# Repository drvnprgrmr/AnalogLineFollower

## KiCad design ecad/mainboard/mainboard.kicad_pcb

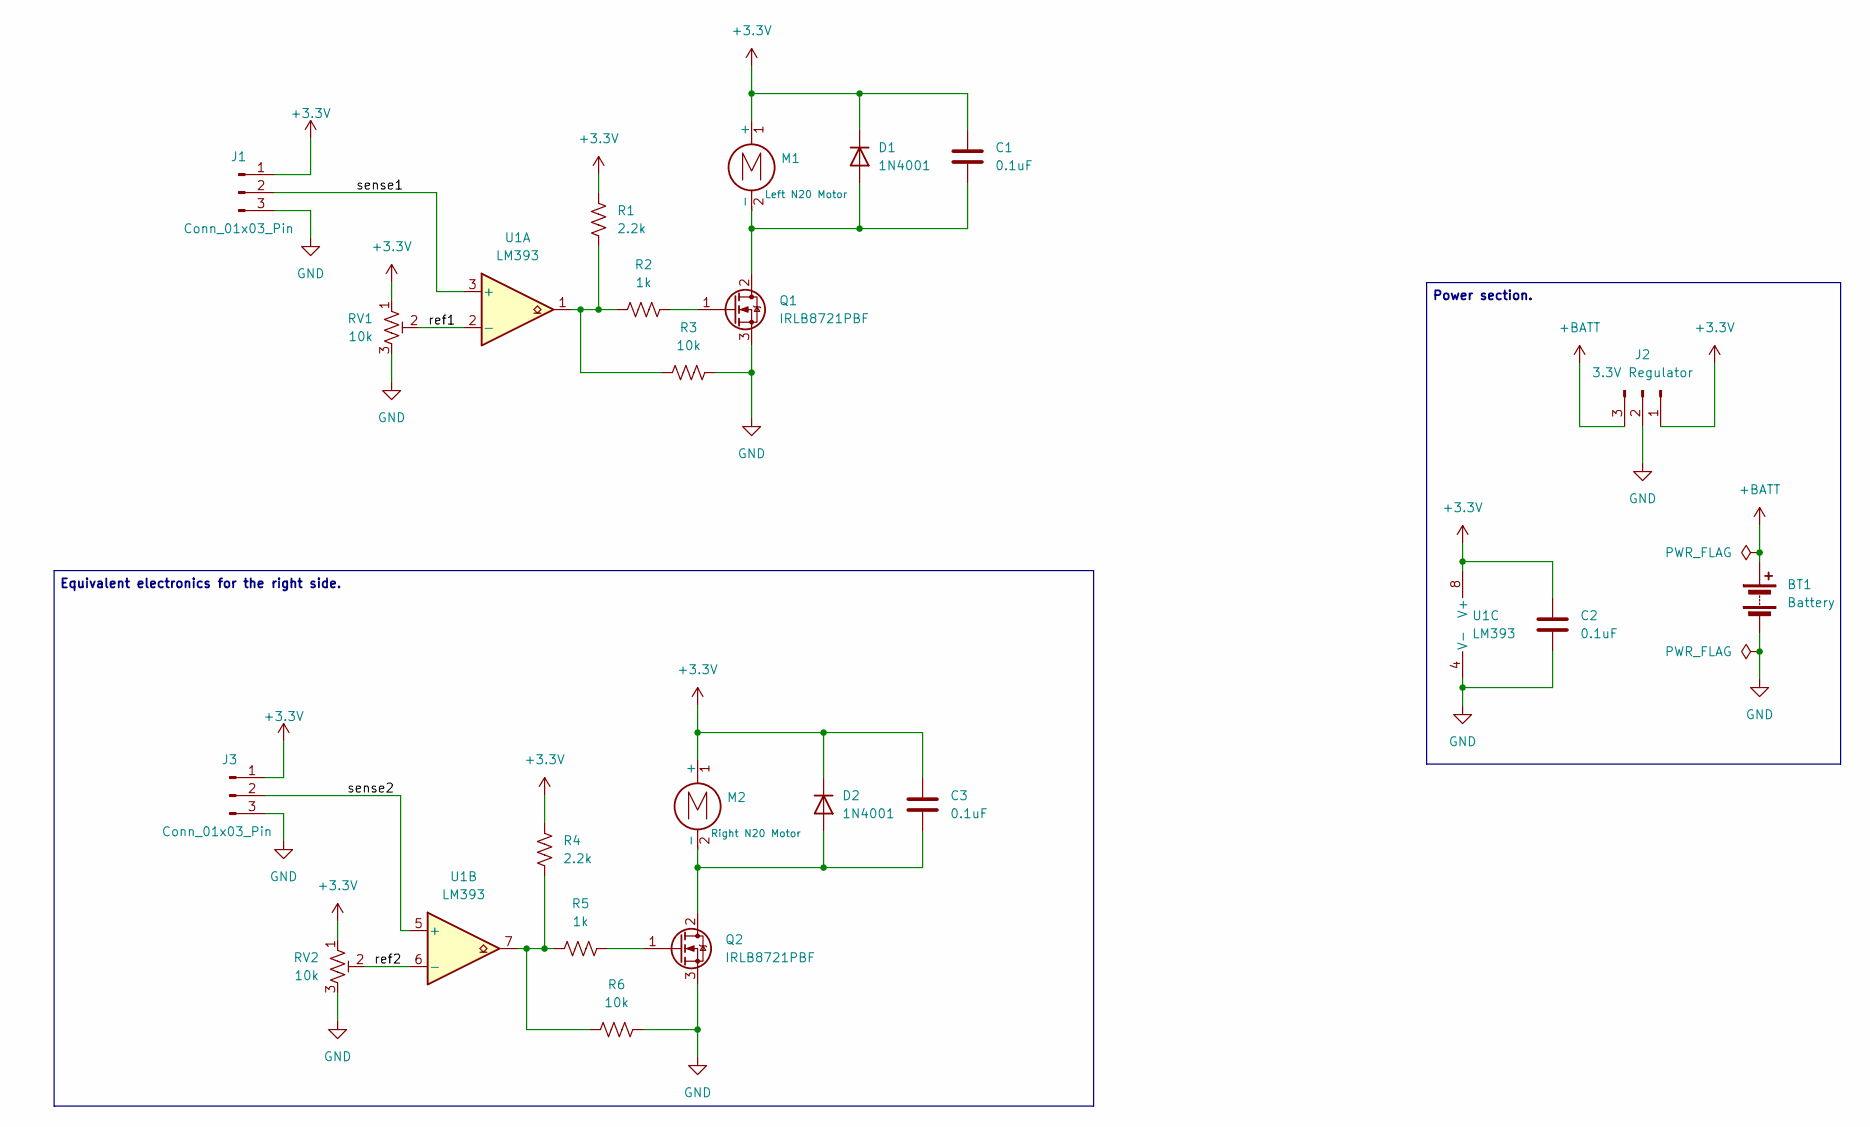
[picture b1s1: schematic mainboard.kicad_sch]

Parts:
BT1: Battery; TerminalBlock_4Ucon_1x02_P3.50mm_Vertical
C1, C2, C3: 0.1uF; C_Radial_D4.0mm_H7.0mm_P1.50mm
D1, D2: 1N4001; D_DO-41_SOD81_P10.16mm_Horizontal
J1, J3: Conn_01x03_Pin; PinHeader_1x03_P2.54mm_Horizontal
J2: 3.3V Regulator; PinHeader_1x03_P2.54mm_Vertical
M1: Left N20 Motor; JST_ZH_B2B-ZR_1x02_P1.50mm_Vertical
M2: Right N20 Motor; JST_ZH_B2B-ZR_1x02_P1.50mm_Vertical
Q1, Q2: IRLB8721PBF; TO-220-3_Vertical
R1, R4: 2.2k; R_Axial_DIN0207_L6.3mm_D2.5mm_P7.62mm_Horizontal
R2, R5: 1k; R_Axial_DIN0207_L6.3mm_D2.5mm_P7.62mm_Horizontal
R3, R6: 10k; R_Axial_DIN0207_L6.3mm_D2.5mm_P7.62mm_Horizontal
RV1, RV2: 10k; Potentiometer_Bourns_3296W_Vertical
U1: LM393; DIP-8_W7.62mm_Socket

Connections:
+3.3V: C1.1, C2.1, C3.1, D1.1 (K), D2.1 (K), J1.1, J2.1, J3.1, M1.1 (+), M2.1 (+), R1.2, R4.2, RV1.1, RV2.1, U1.8 (V+)
+BATT: BT1.1 (+), J2.3
/ref1: RV1.2, U1.2 (-)
/ref2: RV2.2, U1.6 (-)
/sense1: J1.2, U1.3 (+)
/sense2: J3.2, U1.5 (+)
GND: BT1.2 (-), C2.2, J1.3, J2.2, J3.3, Q1.3 (S), Q2.3 (S), R3.2, R6.2, RV1.3, RV2.3, U1.4 (V-)
unnamed: C1.2, D1.2 (A), M1.2 (-), Q1.2 (D)
unnamed: C3.2, D2.2 (A), M2.2 (-), Q2.2 (D)
unnamed: Q1.1 (G), R2.2
unnamed: Q2.1 (G), R5.2
unnamed: R1.1, R2.1, R3.1, U1.1
unnamed: R4.1, R5.1, R6.1, U1.7

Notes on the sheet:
Power section.
Equivalent electronics for the right side.

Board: 12 copper layers, 22 parts (0 on the bottom side), 13 nets, no tracks yet.

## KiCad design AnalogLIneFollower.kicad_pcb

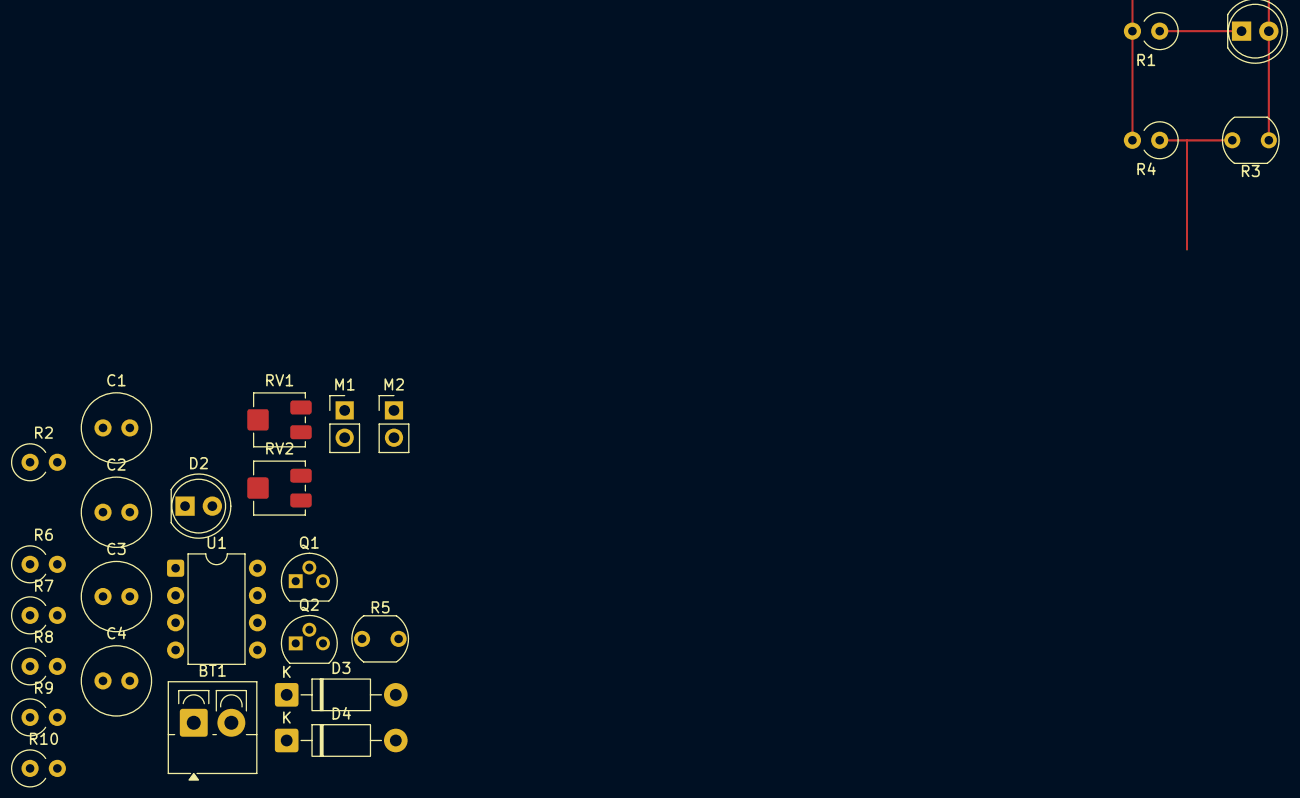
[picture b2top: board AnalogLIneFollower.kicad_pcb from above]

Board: 12 copper layers, 26 parts (0 on the bottom side), 14 nets.

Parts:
BT1: Battery; TerminalBlock_4Ucon_1x02_P3.50mm_Vertical
C1, C2, C3: 0.1uF; C_Radial_D6.3mm_H5.0mm_P2.50mm
C4: 100uF; C_Radial_D6.3mm_H11.0mm_P2.50mm
D1, D2: GREEN; LED_D5.0mm_Clear
D3, D4: 1N4007; D_DO-41_SOD81_P10.16mm_Horizontal
M1: Left Motor; PinHeader_1x02_P2.54mm_Vertical
M2: Right Motor; PinHeader_1x02_P2.54mm_Vertical
Q1, Q2: SS8050; TO-92
R1, R2: 220; R_Axial_DIN0309_L9.0mm_D3.2mm_P2.54mm_Vertical
R3, R5: LDR07; R_LDR_5.1x4.3mm_P3.4mm_Vertical
R4, R6: 10k; R_Axial_DIN0309_L9.0mm_D3.2mm_P2.54mm_Vertical
R7, R8: 100k; R_Axial_DIN0309_L9.0mm_D3.2mm_P2.54mm_Vertical
R9, R10: 1k; R_Axial_DIN0309_L9.0mm_D3.2mm_P2.54mm_Vertical
RV1, RV2: 10k; Potentiometer_Bourns_3214J_Horizontal
U1: LM358; DIP-8_W7.62mm

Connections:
+5V: BT1.1 (+), C1.1, C2.1, C3.1, C4.1, D1.2 (A), D2.2 (A), D3.1 (K), D4.1 (K), M1.1 (+), M2.1 (+), R3.1, R5.1, RV1.1, RV2.1, U1.8 (V+)
/ref1: RV1.2, U1.2 (-)
/ref2: RV2.2, U1.6 (-)
/sense1: R3.2, R4.1, R7.1, U1.3 (+)
/sense2: R5.2, R6.1, R8.1, U1.5 (+)
GND: BT1.2 (-), C3.2, C4.2, Q1.2 (E), Q2.2 (E), R1.2, R2.2, R4.2, R6.2, RV1.3, RV2.3, U1.4 (V-)
unnamed: D1.1 (K), R1.1
unnamed: D2.1 (K), R2.1
unnamed: C1.2, D3.2 (A), M1.2 (-), Q1.3 (C)
unnamed: C2.2, D4.2 (A), M2.2 (-), Q2.3 (C)
unnamed: Q1.1 (B), R9.2
unnamed: Q2.1 (B), R10.2
unnamed: R7.2, R9.1, U1.1
unnamed: R8.2, R10.1, U1.7

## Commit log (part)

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2026-03-08 update schematic with new components
    added decoupling and bulk capacitors
2026-03-08 remove boldface from description text
2026-03-27 change folder structure
2026-03-27 cleanup files and correct .gitignore
2026-03-31 add step files for n20 components
2026-04-01 add general sub-assemblies and begin constructing layout of chasis
2026-04-02 add .history folder to gitignore
2026-04-02 update schematics with smd components
2026-04-03 mcad: add all holes to main lasercut board
2026-04-04 mcad: add stud panel for caster and export 2d drawing of panels
2026-04-06 change operating voltage to 3.3v and add connector for regulator
2026-04-06 ecad: replace diode and mosfet with tht parts
2026-04-07 ecad: update footprints
2026-04-08 update schematic footprints
2026-04-09 work on updated version for the chassis
2026-04-09 create version 2 of lasercut panel
    add image screengrabs of v2
2026-04-10 add a lofi version of a half breadboard to parts lib
2026-04-10 group separate bodies into one part
2026-04-10 add breadboard to assembly
2026-04-13 add export files
